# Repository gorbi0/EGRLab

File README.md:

# Paczka: Kia Sportage EGR → Claude Code

## Instalacja (2 minuty)
1. Rozpakuj do stałego miejsca, np. `~/Projekty/kia-sportage-egr/`.
2. Dorzuć pliki, których nie dało się wyeksportować automatycznie:
   - `schematics/` — PDF Monolith (Kia Sportage od 2010, RU).
   - `logs/raw/` — logi XML z MaxiECU i Car Scanner, które masz lokalnie.
   - `logs/scripts/` — Twoje skrypty Python do parsowania logów (jeśli je zachowałeś).
   - `scope/setups/` — pliki `.stp` z DHO804, gdy je zapiszesz.
   - pliki z wiedzy Projektu claude.ai (pobierz z panelu Projektu) → `docs/` lub `schematics/`.
   - instrukcje Projektu claude.ai (jeśli jakieś ustawiłeś) → dopisz na końcu `CLAUDE.md`.
3. (Opcjonalnie) `git init && git add . && git commit -m "start"` — historia zmian procedury za darmo.
4. W Claude Desktop → zakładka **Code** → wybierz ten folder jako katalog roboczy.
5. Sprawdzenie: zapytaj „Jaki jest stan kampanii i co robię jako pierwsze po powrocie do Hiszpanii?”. Claude powinien odpowiedzieć z `docs/01-overview.md` bez dopytywania.

## Co jest w środku
| Plik | Rola |
|---|---|
| `CLAUDE.md` | Ładowany automatycznie: styl współpracy + import dokumentów 01–03 |
| `docs/01-overview.md` | Aktualny stan, hipotezy H1–H7, następne kroki, decyzje |
| `docs/02-learnings-and-tools.md` | Wnioski, sprzęt, pinout CUD87, strony schematów |
| `docs/03-historia.md` | Chronologia czerwiec–wrzesień 2026 |
| `docs/04-klimatyzacja-ECV.md` | Zamknięta naprawa AC/ECV (ważna dla H1/H7) |
| `docs/05-szarpanie-historia.md` | Diagnostyka szarpania, wykluczenia |
| `docs/procedura_v3_DHO804.md` | Pełna procedura pomiarowa v3 („do auta”) |
| `docs/dziennik-zdarzen.csv` | Dziennik wystąpień P0404 |

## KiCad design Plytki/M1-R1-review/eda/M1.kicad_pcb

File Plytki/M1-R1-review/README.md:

# M1-R1 — jedna płytka LOGGER + TESTER

Wariant M1 (decyzje D-M1-1…13, `Plytki/M1-specyfikacja/`): uproszczony S1 dla świadomego użytkownika, jedna 4-warstwowa płytka, przewody lutowane do pól na PCB, w obudowie jedna listwa śrubowa X1, kable na zewnątrz przez mufy. Obudowa powstanie pod płytkę.

## Schemat (krok 4)

- Jedno źródło: `src/parts.py` (części z `source_ref` pakietów S1). Generator: `scripts/egrlab-docker python3 src/run_schematic.py`.
- Wyniki: `output/pdf/M1-R1-schemat.pdf`, `verification/QA.md`, kontrakt listwy `docs/X1.csv`, mapa pinów `docs/GPIO.csv`, zakupy `docs/zakupy.csv`.
- Kontrole: ERC, netlista pin po pinie (`verify_schematic.py`), `verify_m1.py` (X1, GPIO i piny zakazane, skalowanie kanałów AD7606B i RC, tor prądu, bezpieczny start, wspólne MISO, budżet zasilania, sieci jednopinowe) z próbami ujemnymi i zerową.

## PCB (kroki 5–6)

- Łańcuch layoutu z P07 S1: `src/placement.py` (rozmieszczenie, recenzja użytkownika 8.10: „ok”), `build_board.py`, `route_critical.py` (miedź zablokowana), `fanout_gnd.py`, `prepare_routing.py`, Freerouting 2.1.0, `import_routing.py`, planer `complete_routes.py`, `cleanup.py`, `stitch.py`, `trim_stubs.py`; całość `src/run_layout.py` (`--reuse-ses [--replan]` odtwarza zapisany wynik routera `routing/M1.ses`).
- Płytka 150 × 80 mm, 4 warstwy JLC04161H-7628 (In1 ciągła masa, In2 sygnały), otwory M3 w narożach.
- Górna krawędź: pola przewodów do X1 w kolejności zacisków; prawa: ESP32-S3 DEV-KIT (antena w rogu, strefa bez miedzi, USB-C przy dolnej krawędzi); dolna: pola IBT-2, moduły MAX31856 (zaciski przy krawędzi), moduł microSD (gniazdo przy krawędzi).
- Tor 7,5 A (BAT_P, VBUS, P1_ECU, P1_EGR): wylewki na F.Cu i B.Cu zszyte przelotkami; para Kelvina zablokowana (K_MINUS przez In2.Cu pod masą In1); miedź wokół AD7606B przeniesiona z P05 R3 (to samo ułożenie, przesunięcie +37 / −15 mm) z jego regułami drobnego rastra (0,15 mm tylko w obrysie U3).
- Wydanie: `src/run_release.py` (schemat, layout, nadruk, `verify_pcb.py` z próbami ujemnymi, widoki, `output/pdf/M1-R1-PCB.pdf`, `verification/QA-PCB.md`).

## Po recenzjach M1-R1 (8.10)

- Odpowiedź: `Plytki/M1-specyfikacja/ODPOWIEDZ-NA-RECENZJE-M1-R1.md`. PCB i CAM bez zmian.
- **Montaż (M1-01, decyzja użytkownika):** przed wlutowaniem modułu ESP32 wylutować na nim diodę D1 (USB VBUS → pin 5V listwy); samo USB nie zasila wtedy płytki, programowanie przy włączonym pakiecie.
- **TEST (M1-02, M1-06):** przepięcie listwy według tabeli w SPECYFIKACJI (sekcja 5): pięć żył ECU odłączonych, X1.13 zworką do X1.3.
- **Generator (M1-05):** `build_schematic.py` uzupełnia `eda/M1.kicad_pro` zamiast go nadpisywać; bramka `src/check_pro_preserved.py` w `run_schematic.py`.

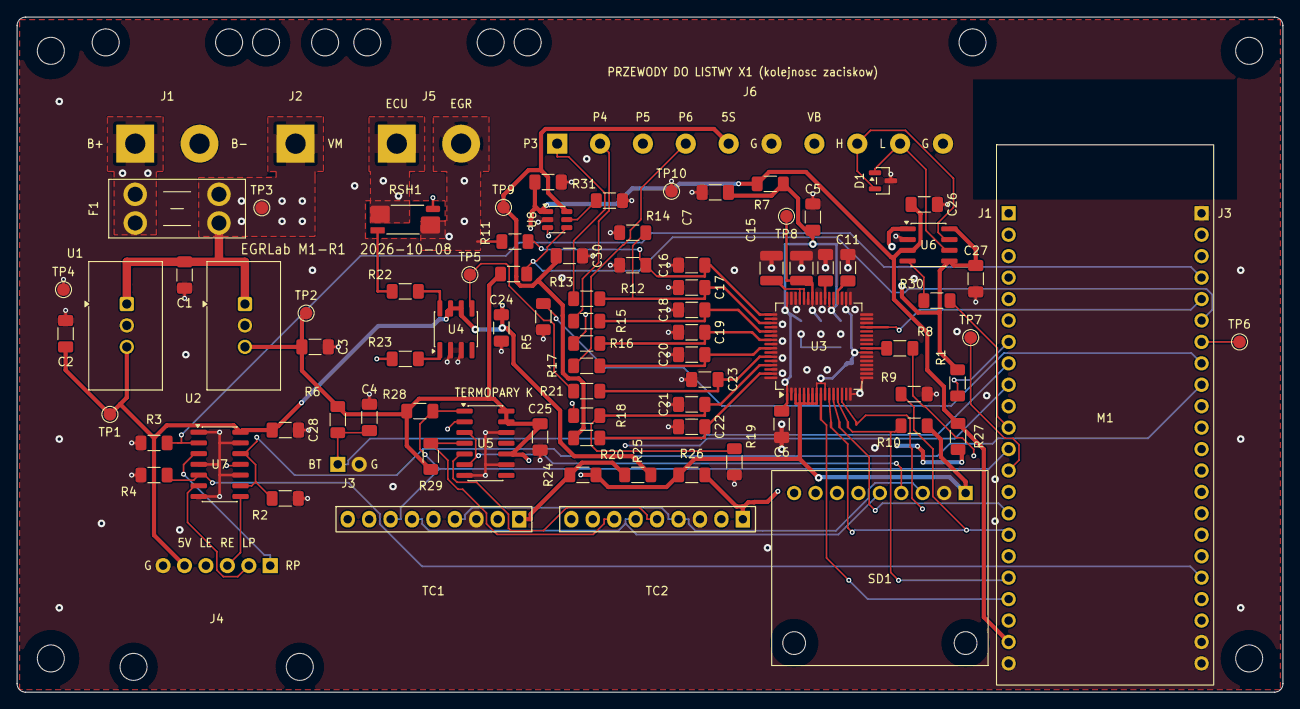
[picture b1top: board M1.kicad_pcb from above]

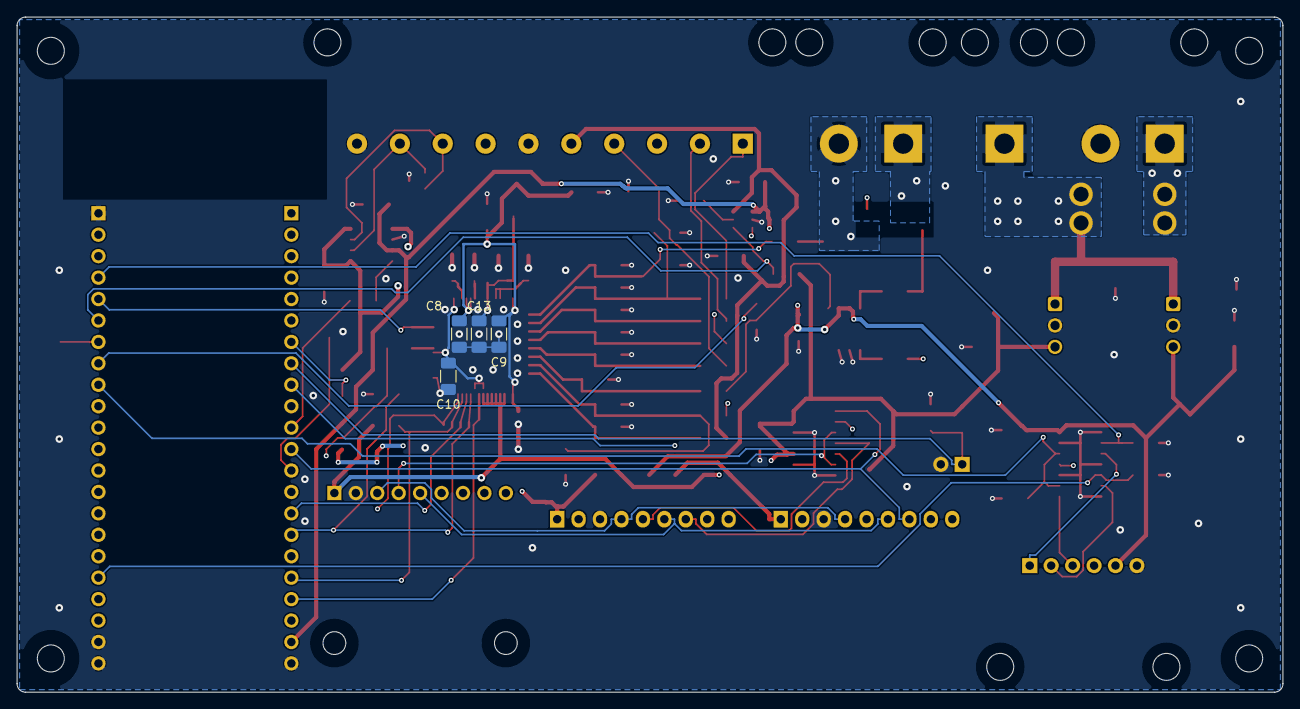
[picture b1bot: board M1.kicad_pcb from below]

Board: 4 copper layers, 150.0 x 80.0 mm, 97 parts (4 on the bottom side), 66 nets.

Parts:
C1: 4.7u; C_1206_3216Metric_Pad1.33x1.80mm_HandSolder
C2, C3, C5: 10u; C_1206_3216Metric_Pad1.33x1.80mm_HandSolder
C4, C6, C7, C8, C9, C10, C13, C24, C25, C26, C27, C28, C29: 100n; C_1206_3216Metric_Pad1.33x1.80mm_HandSolder
C11, C12, C30: 1u; C_1206_3216Metric_Pad1.33x1.80mm_HandSolder
C14, C15: 22u; C_1210_3225Metric
C16, C17, C18, C19, C20, C21, C22: 220p; C_1206_3216Metric_Pad1.33x1.80mm_HandSolder
C23: 1n; C_1206_3216Metric_Pad1.33x1.80mm_HandSolder
D1: PESD2CAN; SOT-23
F1: 7.5A; Fuseholder_Blade_Mini_Keystone_3568
H1, H2, H3, H4: M3 NPTH
J1: BAT; PAD_BAT
J2: VMOTOR; PAD_VMOTOR
J3: BTN; PAD_BTN
J4: IBT-2; PAD_IBT
J5: P1 ECU; PAD_P1
J6: X1.7-16; PAD_SIG
M1: Waveshare ESP32-S3-DEV-KIT-N32R16V; Waveshare_ESP32-S3-DEV-KIT_2x22_W22.86
R1, R6, R9, R28, R29, R32: 10K; R_1206_3216Metric_Pad1.30x1.75mm_HandSolder
R2: 4.7K; R_1206_3216Metric_Pad1.30x1.75mm_HandSolder
R3, R4, R5, R12, R14, R15, R16, R17, R19, R20: 100K; R_1206_3216Metric_Pad1.30x1.75mm_HandSolder
R7: 1R; R_1206_3216Metric_Pad1.30x1.75mm_HandSolder
R8: 33R; R_1206_3216Metric_Pad1.30x1.75mm_HandSolder
R10: 47K; R_1206_3216Metric_Pad1.30x1.75mm_HandSolder
R11, R13: 300K; R_1206_3216Metric_Pad1.30x1.75mm_HandSolder
R18: 499K; R_1206_3216Metric_Pad1.30x1.75mm_HandSolder
R21: 1K; R_1206_3216Metric_Pad1.30x1.75mm_HandSolder
R22, R23: 10R; R_1206_3216Metric_Pad1.30x1.75mm_HandSolder
R24, R25, R26, R27: 0R; R_1206_3216Metric_Pad1.30x1.75mm_HandSolder
R30: 100R; R_1206_3216Metric_Pad1.30x1.75mm_HandSolder
R31: 232K; R_1206_3216Metric_Pad1.30x1.75mm_HandSolder
RSH1: 5m; R_Shunt_Vishay_WSK2512_T1.19mm_SenseE1.70
SD1: Adafruit 4682 microSD (3V); Adafruit_4682_microSD_1x09
TC1: TC1; MAX31856_XU
TC2: TC2; MAX31856_XU
TP1: TP 5V; TestPoint_Pad_D1.5mm
TP2: TP 3V3; TestPoint_Pad_D1.5mm
TP3: TP VBUS; TestPoint_Pad_D1.5mm
TP4, TP10: TP GND; TestPoint_Pad_D1.5mm
TP5: TP I_MOT; TestPoint_Pad_D1.5mm
TP6: TP SCOPE_TRIG; TestPoint_Pad_D1.5mm
TP7: TP GPIO3_TP; TestPoint_Pad_D1.5mm
TP8: TP ADC_REF; TestPoint_Pad_D1.5mm
TP9: TP SENS_5V; TestPoint_Pad_D1.5mm
U1: TSR 2-2450; Converter_DCDC_TRACO_TSR2-xxxx_THT
U2: TSR 2-2433; Converter_DCDC_TRACO_TSR2-xxxx_THT
U3: AD7606BBSTZ; LQFP-64_10x10mm_P0.5mm
U4: INA240A2; SOIC-8_3.9x4.9mm_P1.27mm
U5: 74LVC125AD; SOIC-14_3.9x8.7mm_P1.27mm
U6: TCAN1051V; SOIC-8_3.9x4.9mm_P1.27mm
U7: 74AHCT125D; SOIC-14_3.9x8.7mm_P1.27mm
U8: TPS2553DBVR; SOT-23-6

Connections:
3V3: C3.1, C10.1, C25.1, C27.1, R1.2, R6.2, R10.2, R24.1, R26.1, R28.2, R29.2, R32.2, SD1.1, TP2.1, U2.3, U3.3, U3.4, U3.5, U3.6, U3.7, U3.8, U3.10, U3.23, U3.34, U5.10, U5.13, U5.14, U6.1, U6.5, U6.8
5V: C2.1, C24.1, C26.1, C28.1, C29.1, J4.5, M1.J1-21, R7.1, R25.1, R27.1, TP1.1, U1.3, U4.6, U4.7, U6.3, U7.14, U8.1
5VA: C5.1, C6.1, C7.1, C8.1, C9.1, R7.2, U3.1, U3.37, U3.38, U3.48
/ADC/ADC_CH1: C16.1, R11.2, R12.1, U3.49
/ADC/ADC_CH2: C17.1, R13.2, R14.1, U3.51
/ADC/ADC_CH3: C18.1, R15.2, U3.53
/ADC/ADC_CH4: C19.1, R16.2, U3.55
/ADC/ADC_CH5: C20.1, R17.2, U3.57
/ADC/ADC_CH6: C23.1, R21.2, U3.59
/ADC/ADC_CH7: C21.1, R18.2, R19.1, U3.61
/ADC/ADC_CH8: C22.1, R20.2, U3.63
/ADC/ADC_DOUTA_U: R8.1, U3.24
/ADC/REFCAP: C15.1, U3.44, U3.45
/ADC/REGCAP_A: C11.1, U3.36
/ADC/REGCAP_D: C12.1, U3.39
/BAT_P: F1.1, J1.1
/MCU/BTN: C4.1, J3.1, M1.J1-8, R6.1
/MCU/SD_CS: M1.J1-7, R1.1, SD1.6
/NAPED/IBT_LEN: J4.4, U7.11
/NAPED/IBT_LPWM: J4.2, U7.6
/NAPED/IBT_REN: J4.3, U7.8
/NAPED/IBT_RPWM: J4.1, U7.3
/NAPED/ILIM: R31.1, U8.5
/PRAD/INA_MINUS: R23.2, U4.1
/PRAD/INA_PLUS: R22.2, U4.8
/PRAD/K_MINUS: R23.1, RSH1.3
/PRAD/K_PLUS: R22.1, RSH1.2
/TEMP_CAN/CAN_RX_U: R30.1, U6.4
/TEMP_CAN/TC1_SDO: TC1.5, U5.2
/TEMP_CAN/TC2_SDO: TC2.5, U5.5
ADC_BUSY: M1.J1-20, U3.14
ADC_CONVST: M1.J1-19, U3.9
ADC_CS: M1.J1-18, R10.1, U3.13
ADC_DOUTA: M1.J1-17, R8.2
ADC_REF: C13.1, C14.1, TP8.1, U3.42
ADC_RESET: M1.J1-16, R9.1, U3.11
ADC_SCLK: M1.J1-15, U3.12
ADC_SDI: M1.J3-5, U3.29
CAN_H: D1.2, J6.8, U6.7
CAN_L: D1.1, J6.9, U6.6
CAN_RXD: M1.J1-11, R30.2
DRIVE_EN: M1.J3-9, R2.1, U7.9, U7.12
GND: C1.2, C2.2, C3.2, C4.2, C5.2, C6.2, C7.2, C8.2, C9.2, C10.2, C11.2, C12.2, C13.2, C14.2, C15.2, C16.2, C17.2, C18.2, C19.2, C20.2, C21.2, C22.2, C23.2, C24.2, C25.2, C26.2, C27.2, C28.2, C29.2, C30.2, D1.3, J1.2, J3.2, J4.6, J6.6, J6.10, M1.J1-22, M1.J3-1, M1.J3-21, M1.J3-22, R2.2, R3.2, R4.2, R5.2, R9.2, R12.2, R14.2, R19.2, R31.2, SD1.2, TC1.3, TC2.3, TP4.1, TP10.1, U1.2, U2.2, U3.2, U3.16, U3.17, U3.18, U3.19, U3.20, U3.21, U3.22, U3.26, U3.30, U3.31, U3.32, U3.33, U3.35, U3.40, U3.41, U3.43, U3.46, U3.47, U3.50, U3.52, U3.54, U3.56, U3.58, U3.60, U3.62, U3.64, U4.2, U4.3, U5.7, U5.9, U5.12, U6.2, U7.1, U7.4, U7.7, U7.10, U7.13, U8.2
GPIO3_TP: M1.J1-13, TP7.1
I_MOT: R21.1, TP5.1, U4.5
LPWM: M1.J3-18, R4.1, U7.5
P1_ECU: J5.1, RSH1.1
P1_EGR: J5.2, R11.1, RSH1.4
P3: J6.1, R13.1
P4: J6.2, R15.1
P5: J6.3, R16.1
P6: J6.4, R17.1
RPWM: M1.J3-4, R3.1, U7.2
SCOPE_TRIG: M1.J3-7, TP6.1
SENS_5V: C30.1, J6.5, R20.1, TP9.1, U8.6
SENS_EN: M1.J3-8, R5.1, U8.3
SENS_FAULT_N: M1.J3-6, R32.1, U8.4
SPI3_MISO: M1.J1-6, SD1.4, U5.3, U5.6
SPI3_MOSI: M1.J1-5, SD1.5, TC1.6, TC2.6
SPI3_SCK: M1.J1-4, SD1.3, TC1.4, TC2.4
TC1_CS: M1.J1-12, R28.1, TC1.7, U5.1
TC1_VIN: R24.2, R25.2, TC1.1
TC2_CS: M1.J1-9, R29.1, TC2.7, U5.4
TC2_VIN: R26.2, R27.2, TC2.1
VBAT_CAR: J6.7, R18.1
VBUS: C1.1, F1.2, J2.1, TP3.1, U1.1, U2.1

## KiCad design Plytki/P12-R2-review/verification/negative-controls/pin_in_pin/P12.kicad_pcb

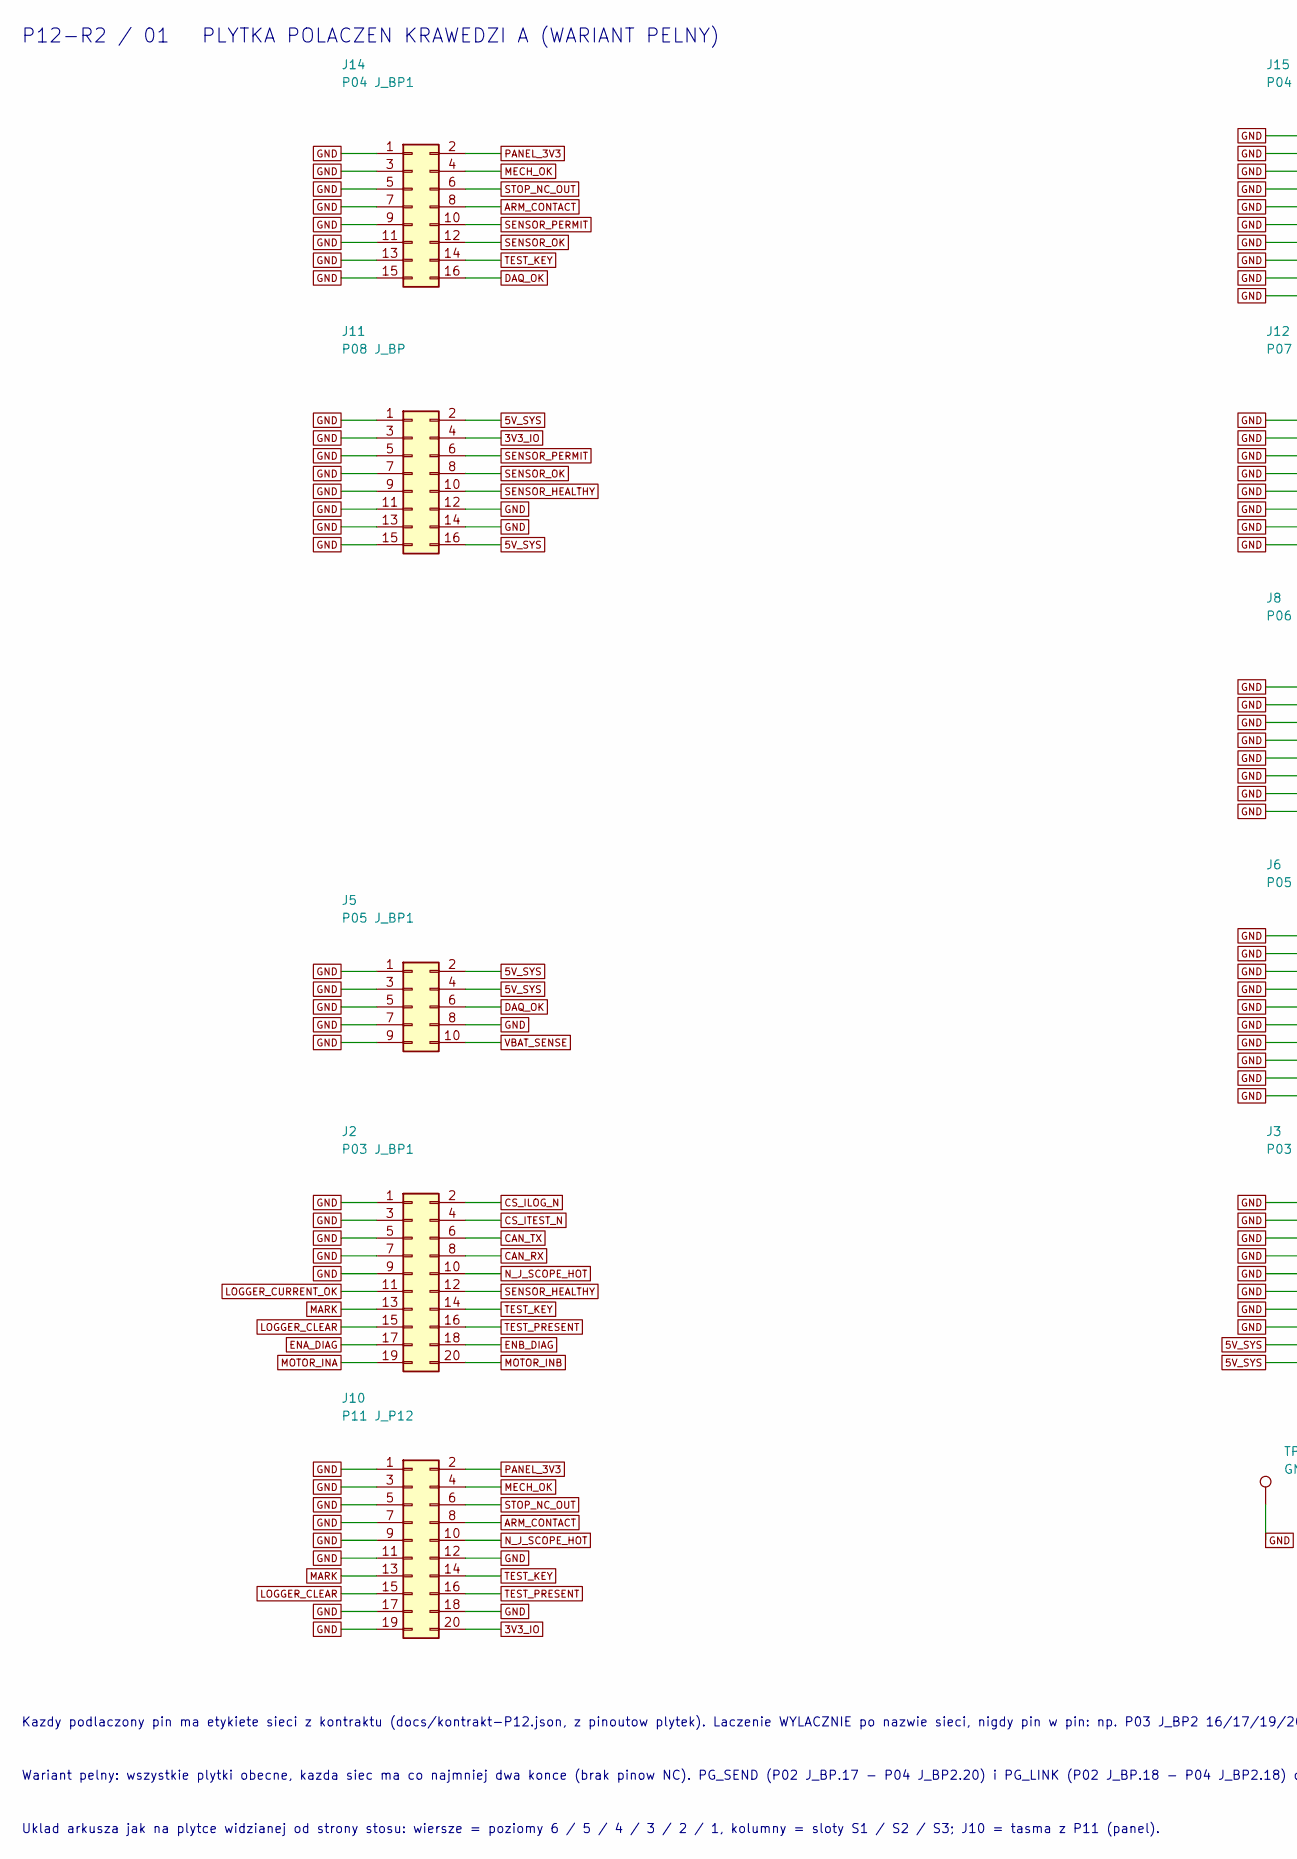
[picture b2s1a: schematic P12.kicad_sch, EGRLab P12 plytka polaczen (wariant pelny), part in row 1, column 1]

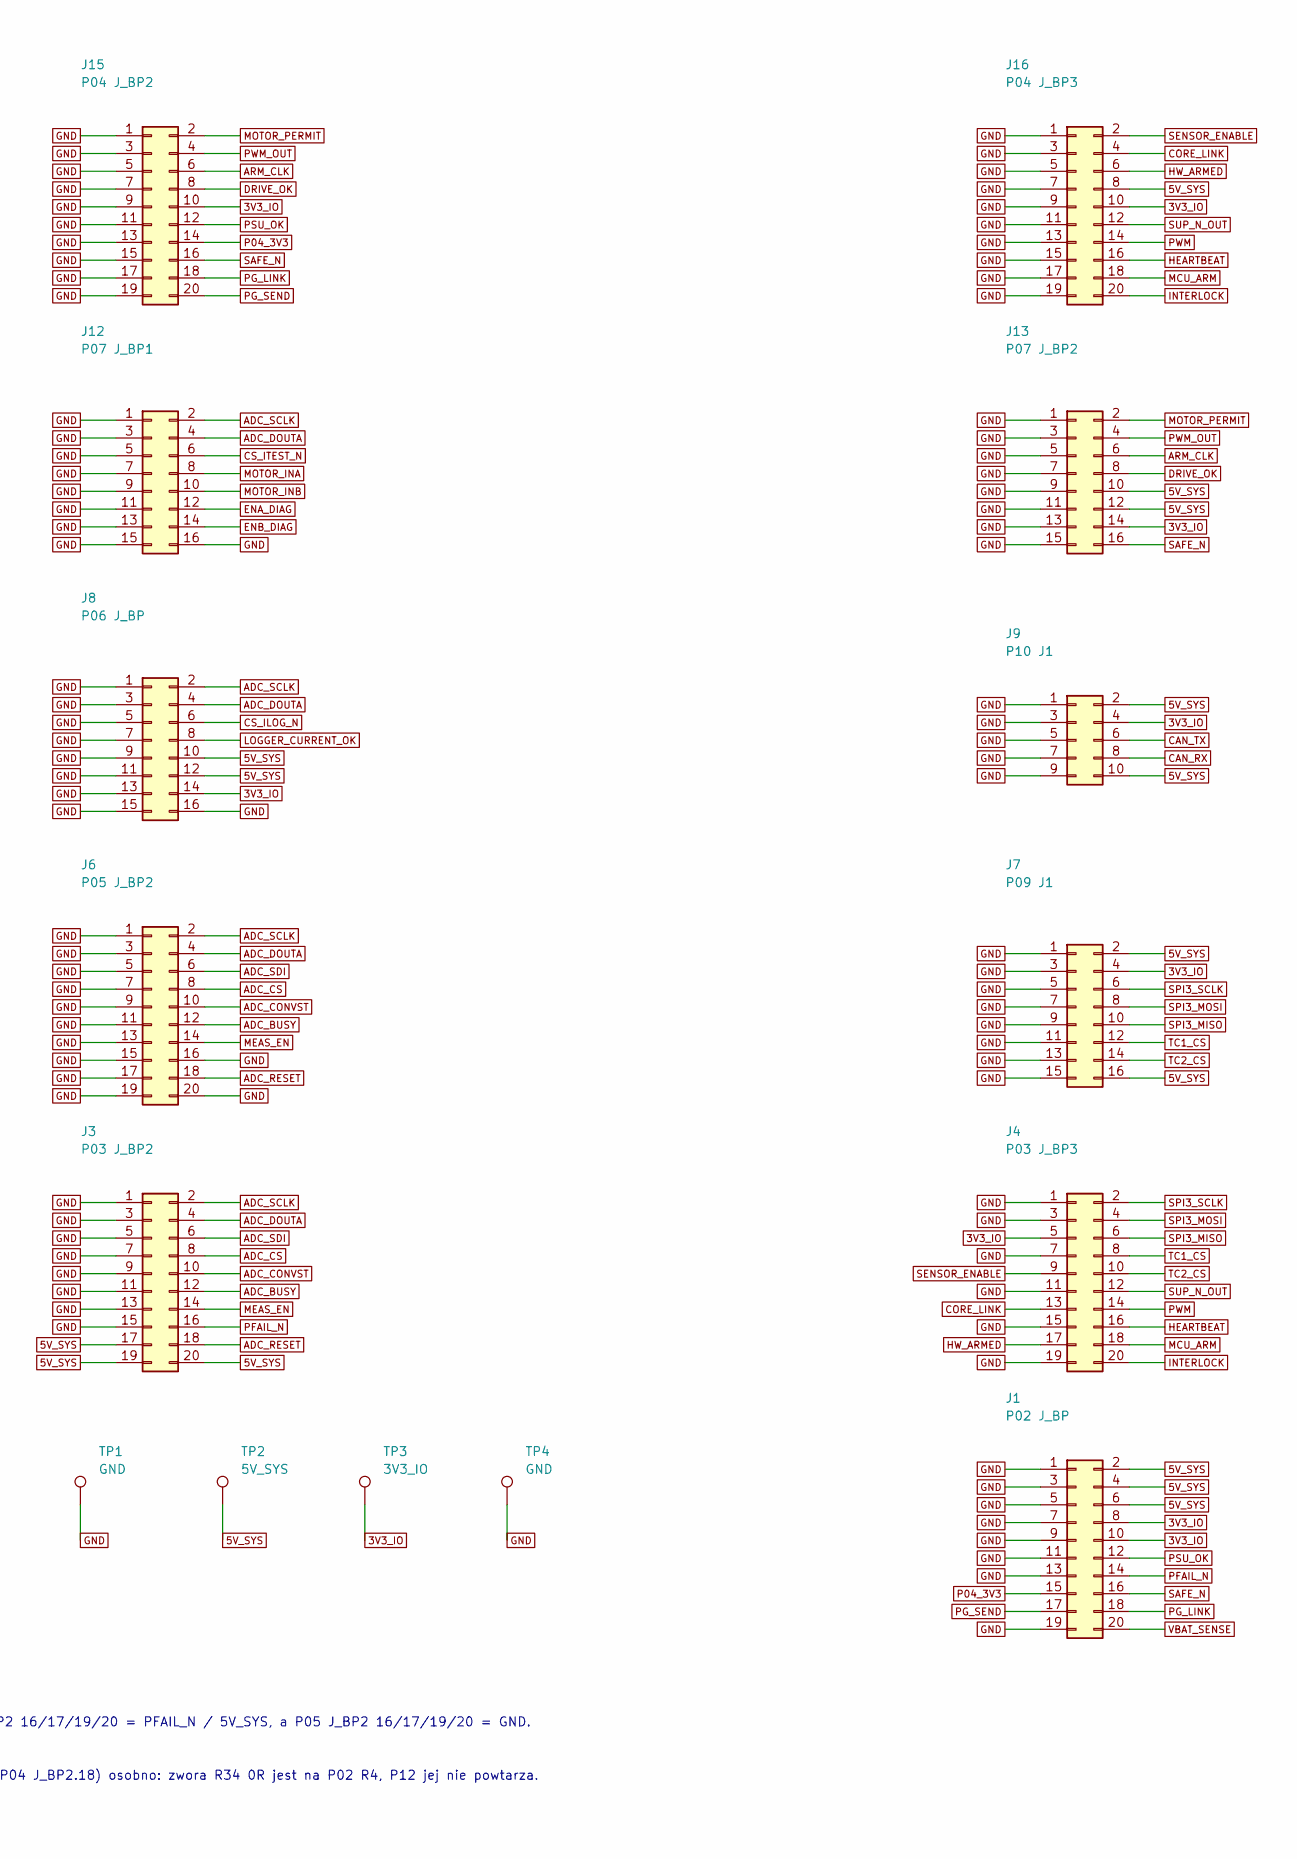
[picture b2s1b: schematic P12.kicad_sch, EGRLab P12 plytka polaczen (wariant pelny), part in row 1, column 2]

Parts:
J1: P02 J_BP; IDC-Header_2x10_P2.54mm_Vertical; MPN Amphenol FCI T821120A1S100CEU (IDC 2x10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
J2: P03 J_BP1; IDC-Header_2x10_P2.54mm_Vertical; MPN Amphenol FCI T821120A1S100CEU (IDC 2x10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
J3: P03 J_BP2; IDC-Header_2x10_P2.54mm_Vertical; MPN Amphenol FCI T821120A1S100CEU (IDC 2x10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
J4: P03 J_BP3; IDC-Header_2x10_P2.54mm_Vertical; MPN Amphenol FCI T821120A1S100CEU (IDC 2x10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
J5: P05 J_BP1; IDC-Header_2x05_P2.54mm_Vertical; MPN Amphenol FCI T821110A1S100CEU (IDC 2x5 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
J6: P05 J_BP2; IDC-Header_2x10_P2.54mm_Vertical; MPN Amphenol FCI T821120A1S100CEU (IDC 2x10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
J7: P09 J1; IDC-Header_2x08_P2.54mm_Vertical; MPN Amphenol FCI T821116A1S100CEU (IDC 2x8 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
J8: P06 J_BP; IDC-Header_2x08_P2.54mm_Vertical; MPN Amphenol FCI T821116A1S100CEU (IDC 2x8 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
J9: P10 J1; IDC-Header_2x05_P2.54mm_Vertical; MPN Amphenol FCI T821110A1S100CEU (IDC 2x5 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
J10: P11 J_P12; IDC-Header_2x10_P2.54mm_Vertical; MPN Amphenol FCI T821120A1S100CEU (IDC 2x10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
J11: P08 J_BP; IDC-Header_2x08_P2.54mm_Vertical; MPN Amphenol FCI T821116A1S100CEU (IDC 2x8 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
J12: P07 J_BP1; IDC-Header_2x08_P2.54mm_Vertical; MPN Amphenol FCI T821116A1S100CEU (IDC 2x8 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
J13: P07 J_BP2; IDC-Header_2x08_P2.54mm_Vertical; MPN Amphenol FCI T821116A1S100CEU (IDC 2x8 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
J14: P04 J_BP1; IDC-Header_2x08_P2.54mm_Vertical; MPN Amphenol FCI T821116A1S100CEU (IDC 2x8 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
J15: P04 J_BP2; IDC-Header_2x10_P2.54mm_Vertical; MPN Amphenol FCI T821120A1S100CEU (IDC 2x10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
J16: P04 J_BP3; IDC-Header_2x10_P2.54mm_Vertical; MPN Amphenol FCI T821120A1S100CEU (IDC 2x10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
TP1, TP4: GND; TestPoint_THTPad_D2.0mm_Drill1.0mm; MPN pole pomiarowe THT D2,0 / otwór 1,0 (be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
TP2: 5V_SYS; TestPoint_THTPad_D2.0mm_Drill1.0mm; MPN pole pomiarowe THT D2,0 / otwór 1,0 (be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
TP3: 3V3_IO; TestPoint_THTPad_D2.0mm_Drill1.0mm; MPN pole pomiarowe THT D2,0 / otwór 1,0 (be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

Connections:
3V3_IO: J1.8, J1.10, J4.5, J7.4, J8.14, J9.4, J10.20, J11.4, J13.14, J15.10, J16.10, TP3.1
5V_SYS: J1.2, J1.4, J1.6, J3.17, J3.19, J3.20, J5.2, J5.4, J7.2, J7.16, J8.10, J8.12, J9.2, J9.10, J11.2, J11.16, J13.10, J13.12, J16.8, TP2.1
ADC_BUSY: J3.12, J6.12
ADC_CONVST: J3.10, J6.10
ADC_CS: J3.8, J6.8
ADC_DOUTA: J3.4, J6.4, J8.4, J12.4
ADC_RESET: J3.18, J6.18
ADC_SCLK: J3.2, J6.2, J8.2, J12.2
ADC_SDI: J3.6, J6.6
ARM_CLK: J13.6, J15.6
ARM_CONTACT: J10.8, J14.8
CAN_RX: J2.8, J9.8
CAN_TX: J2.6, J9.6
CORE_LINK: J4.13, J16.4
CS_ILOG_N: J2.2, J8.6
CS_ITEST_N: J2.4, J12.6
DAQ_OK: J5.6, J14.16
DRIVE_OK: J13.8, J15.8
ENA_DIAG: J2.17, J12.12
ENB_DIAG: J2.18, J12.14
GND: J1.1, J1.3, J1.5, J1.7, J1.9, J1.11, J1.13, J1.19, J2.1, J2.3, J2.5, J2.7, J2.9, J3.1, J3.3, J3.5, J3.7, J3.9, J3.11, J3.13, J3.15, J4.1, J4.3, J4.7, J4.11, J4.15, J4.19, J5.1, J5.3, J5.5, J5.7, J5.8, J5.9, J6.1, J6.3, J6.5, J6.7, J6.9, J6.11, J6.13, J6.15, J6.16, J6.17, J6.19, J6.20, J7.1, J7.3, J7.5, J7.7, J7.9, J7.11, J7.13, J7.15, J8.1, J8.3, J8.5, J8.7, J8.9, J8.11, J8.13, J8.15, J8.16, J9.1, J9.3, J9.5, J9.7, J9.9, J10.1, J10.3, J10.5, J10.7, J10.9, J10.11, J10.12, J10.17, J10.18, J10.19, J11.1, J11.3, J11.5, J11.7, J11.9, J11.11, J11.12, J11.13, J11.14, J11.15, J12.1, J12.3, J12.5, J12.7, J12.9, J12.11, J12.13, J12.15, J12.16, J13.1, J13.3, J13.5, J13.7, J13.9, J13.11, J13.13, J13.15, J14.1, J14.3, J14.5, J14.7, J14.9, J14.11, J14.13, J14.15, J15.1, J15.3, J15.5, J15.7, J15.9, J15.11, J15.13, J15.15, J15.17, J15.19, J16.1, J16.3, J16.5, J16.7, J16.9, J16.11, J16.13, J16.15, J16.17, J16.19, TP1.1, TP4.1
HEARTBEAT: J4.16, J16.16
HW_ARMED: J4.17, J16.6
INTERLOCK: J4.20, J16.20
LOGGER_CLEAR: J2.15, J10.15
LOGGER_CURRENT_OK: J2.11, J8.8
MARK: J2.13, J10.13
MCU_ARM: J4.18, J16.18
MEAS_EN: J3.14, J6.14
MECH_OK: J10.4, J14.4
MOTOR_INA: J2.19, J12.8
MOTOR_INB: J2.20, J12.10
MOTOR_PERMIT: J13.2, J15.2
N_J_SCOPE_HOT: J2.10, J10.10
P04_3V3: J1.15, J15.14
PANEL_3V3: J10.2, J14.2
PFAIL_N: J1.14, J3.16
PG_LINK: J1.18, J15.18
PG_SEND: J1.17, J15.20
PSU_OK: J1.12, J15.12
PWM: J4.14, J16.14
PWM_OUT: J13.4, J15.4
SAFE_N: J1.16, J13.16, J15.16
SENSOR_ENABLE: J4.9, J16.2
SENSOR_HEALTHY: J2.12, J11.10
SENSOR_OK: J11.8, J14.12
SENSOR_PERMIT: J11.6, J14.10
SPI3_MISO: J4.6, J7.10
SPI3_MOSI: J4.4, J7.8
SPI3_SCLK: J4.2, J7.6
STOP_NC_OUT: J10.6, J14.6
SUP_N_OUT: J4.12, J16.12
TC1_CS: J4.8, J7.12
TC2_CS: J4.10, J7.14
TEST_KEY: J2.14, J10.14, J14.14
TEST_PRESENT: J2.16, J10.16
VBAT_SENSE: J1.20, J5.10

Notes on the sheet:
Kazdy podlaczony pin ma etykiete sieci z kontraktu (docs/kontrakt-P12.json, z pinoutow plytek). Laczenie WYLACZNIE po nazwie sieci, nigdy pin w pin: np. P03 J_BP2 16/17/19/20 = PFAIL_N / 5V_SYS, a P05 J_BP2 16/17/19/20 = GND.
Wariant pelny: wszystkie plytki obecne, kazda siec ma co najmniej dwa konce (brak pinow NC). PG_SEND (P02 J_BP.17 - P04 J_BP2.20) i PG_LINK (P02 J_BP.18 - P04 J_BP2.18) osobno: zwora R34 0R jest na P02 R4, P12 jej nie powtarza.
Uklad arkusza jak na plytce widzianej od strony stosu: wiersze = poziomy 6 / 5 / 4 / 3 / 2 / 1, kolumny = sloty S1 / S2 / S3; J10 = tasma z P11 (panel).
P12-R2 / 01 PLYTKA POLACZEN KRAWEDZI A (WARIANT PELNY)

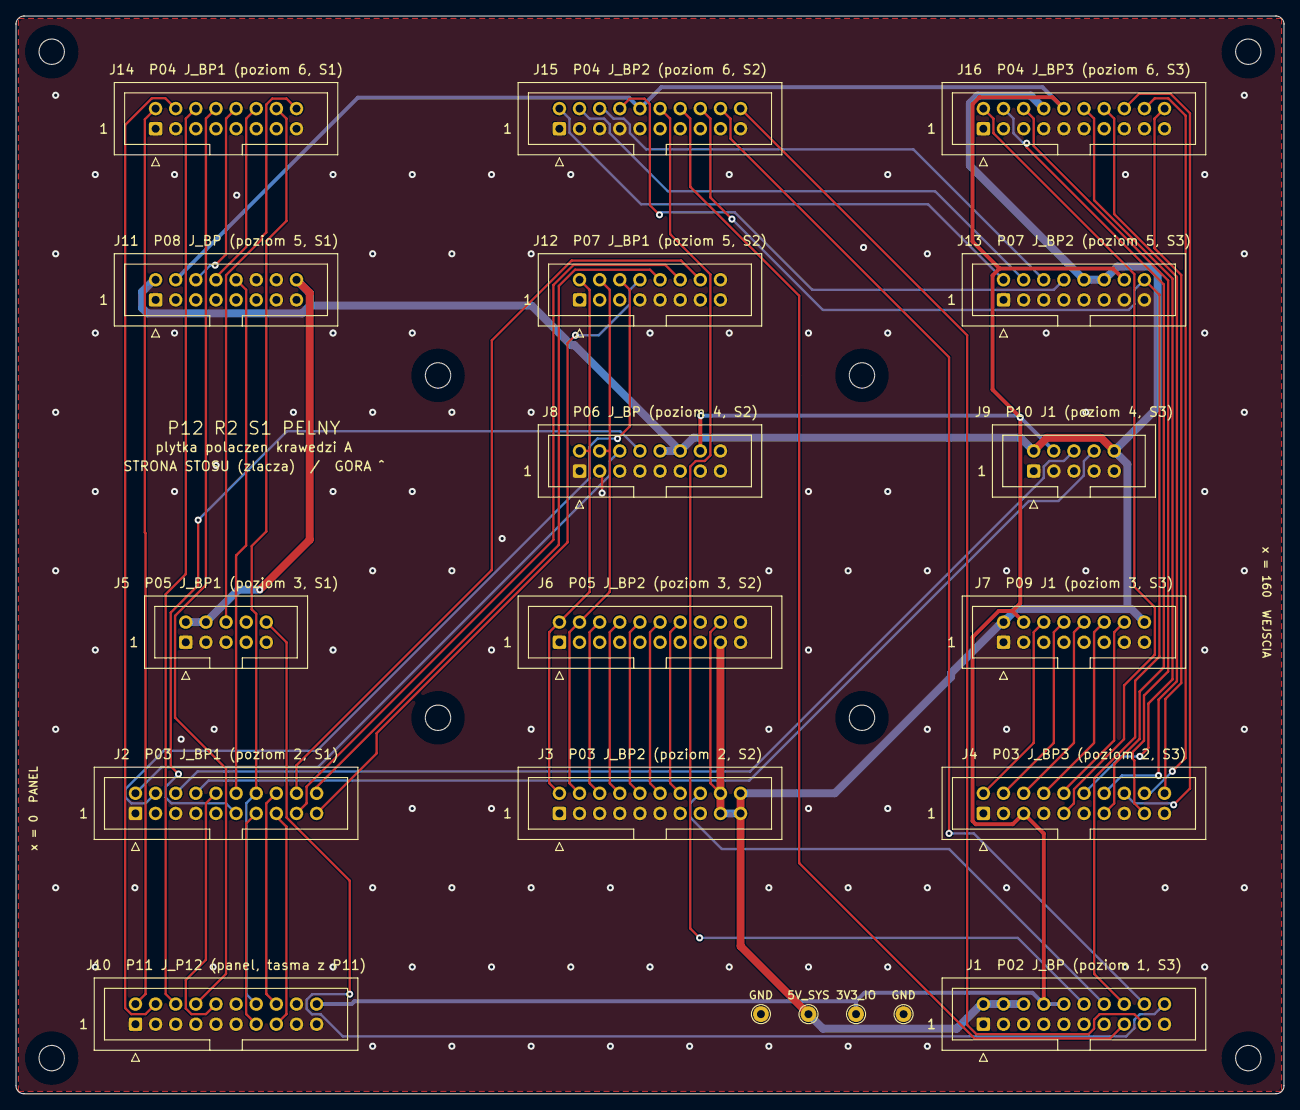
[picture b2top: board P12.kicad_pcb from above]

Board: 2 copper layers, 160.0 x 136.0 mm, 28 parts (0 on the bottom side), 57 nets.

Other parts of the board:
H1, H2, H3, H4, H5, H6, H7, H8: M3 NPTH
